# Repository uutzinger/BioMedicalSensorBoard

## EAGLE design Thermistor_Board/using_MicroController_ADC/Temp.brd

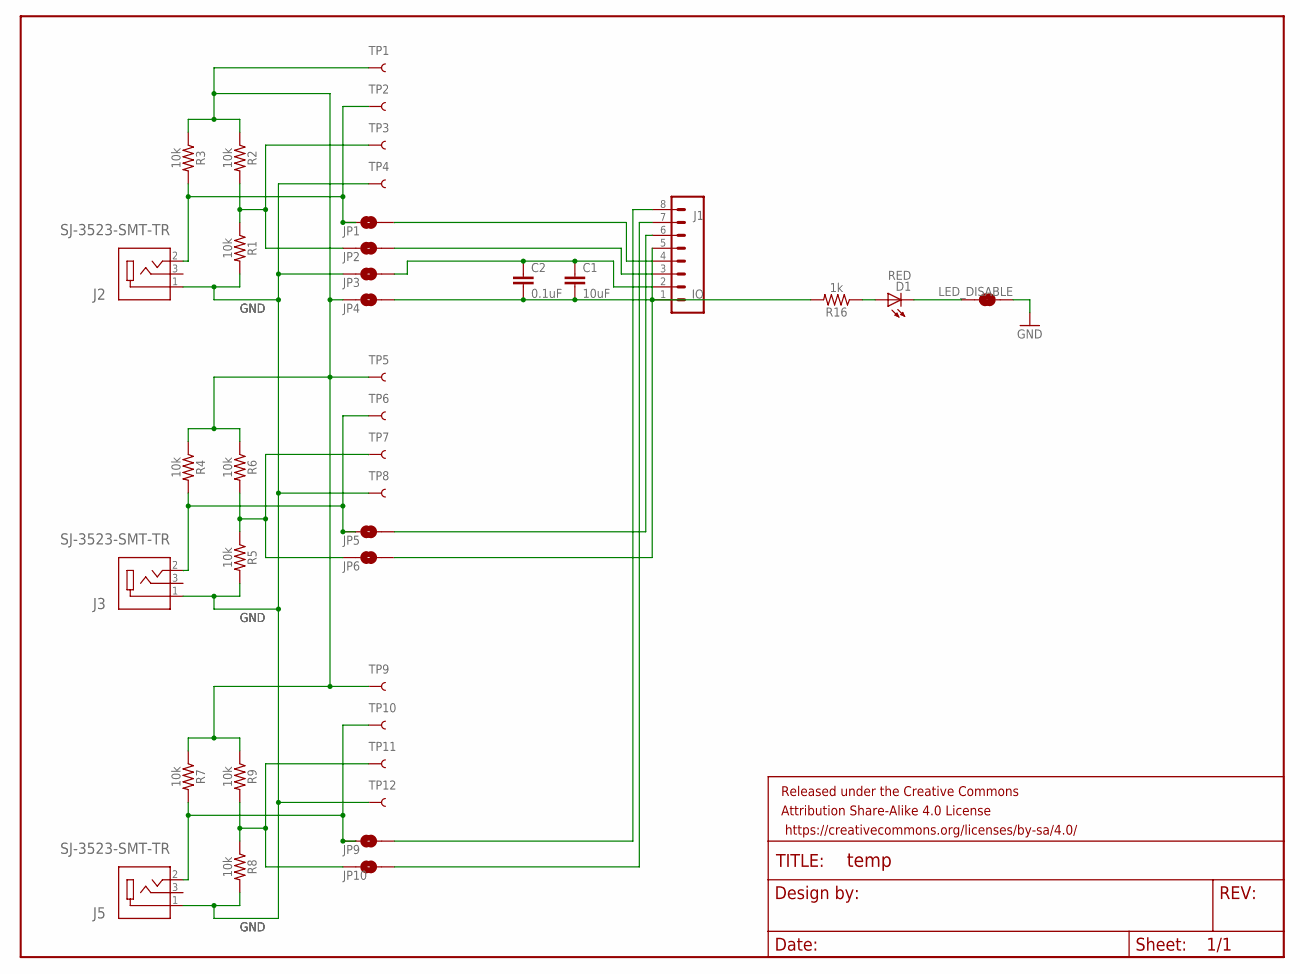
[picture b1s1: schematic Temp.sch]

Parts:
C1: 10uF; 0603
C2: 0.1uF; 0603
D1: RED; LED-0603
FRAME1: FRAME-LETTERNO_PACKAGE; DUMMY
J1: IO; 1X08
J2, J3, J5: SJ-3523-SMT-TR; CUI_SJ-3523-SMT-TR
JP1, JP2, JP3, JP4, JP5, JP6, JP9, JP10: JUMPER-SMT_2_NO_NO-SILK; SMT-JUMPER_2_NO_NO-SILK
LED_DISABLE: JUMPER-SMT_2_NC_TRACE_SILK; SMT-JUMPER_2_NC_TRACE_SILK
R1, R2, R3, R4, R5, R6, R7, R8, R9: 10k; 0603
R16: 1k; 0603
TP1, TP2, TP3, TP4, TP5, TP6, TP7, TP8, TP9, TP10, TP11, TP12: TEST-POINT3X5; PAD.03X.05

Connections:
3.3V: JP4.1, R2.1, R3.1, R4.1, R6.1, R7.1, R9.1, TP1.P$1, TP5.P$1, TP9.P$1
GND: J2.1, J3.1, J5.1, JP3.1, LED_DISABLE.1, R1.2, R5.2, R8.2, TP4.P$1, TP8.P$1, TP12.P$1
unnamed: JP6.1, R5.1, R6.2, TP7.P$1
unnamed: JP2.1, R1.1, R2.2, TP3.P$1
unnamed: J1.3, JP2.2
unnamed: J2.2, JP1.1, R3.2, TP2.P$1
unnamed: J1.4, JP1.2
unnamed: J3.2, JP5.1, R4.2, TP6.P$1
unnamed: J1.7, JP10.2
unnamed: J1.8, JP9.2
unnamed: J1.6, JP5.2
unnamed: JP10.1, R8.1, R9.2, TP11.P$1
unnamed: J5.2, JP9.1, R7.2, TP10.P$1
unnamed: C1.2, C2.2, J1.1, JP4.2, R16.2
unnamed: C1.1, C2.1, J1.2, J1.5, JP3.2, JP6.2
unnamed: D1.A, R16.1
unnamed: D1.C, LED_DISABLE.2

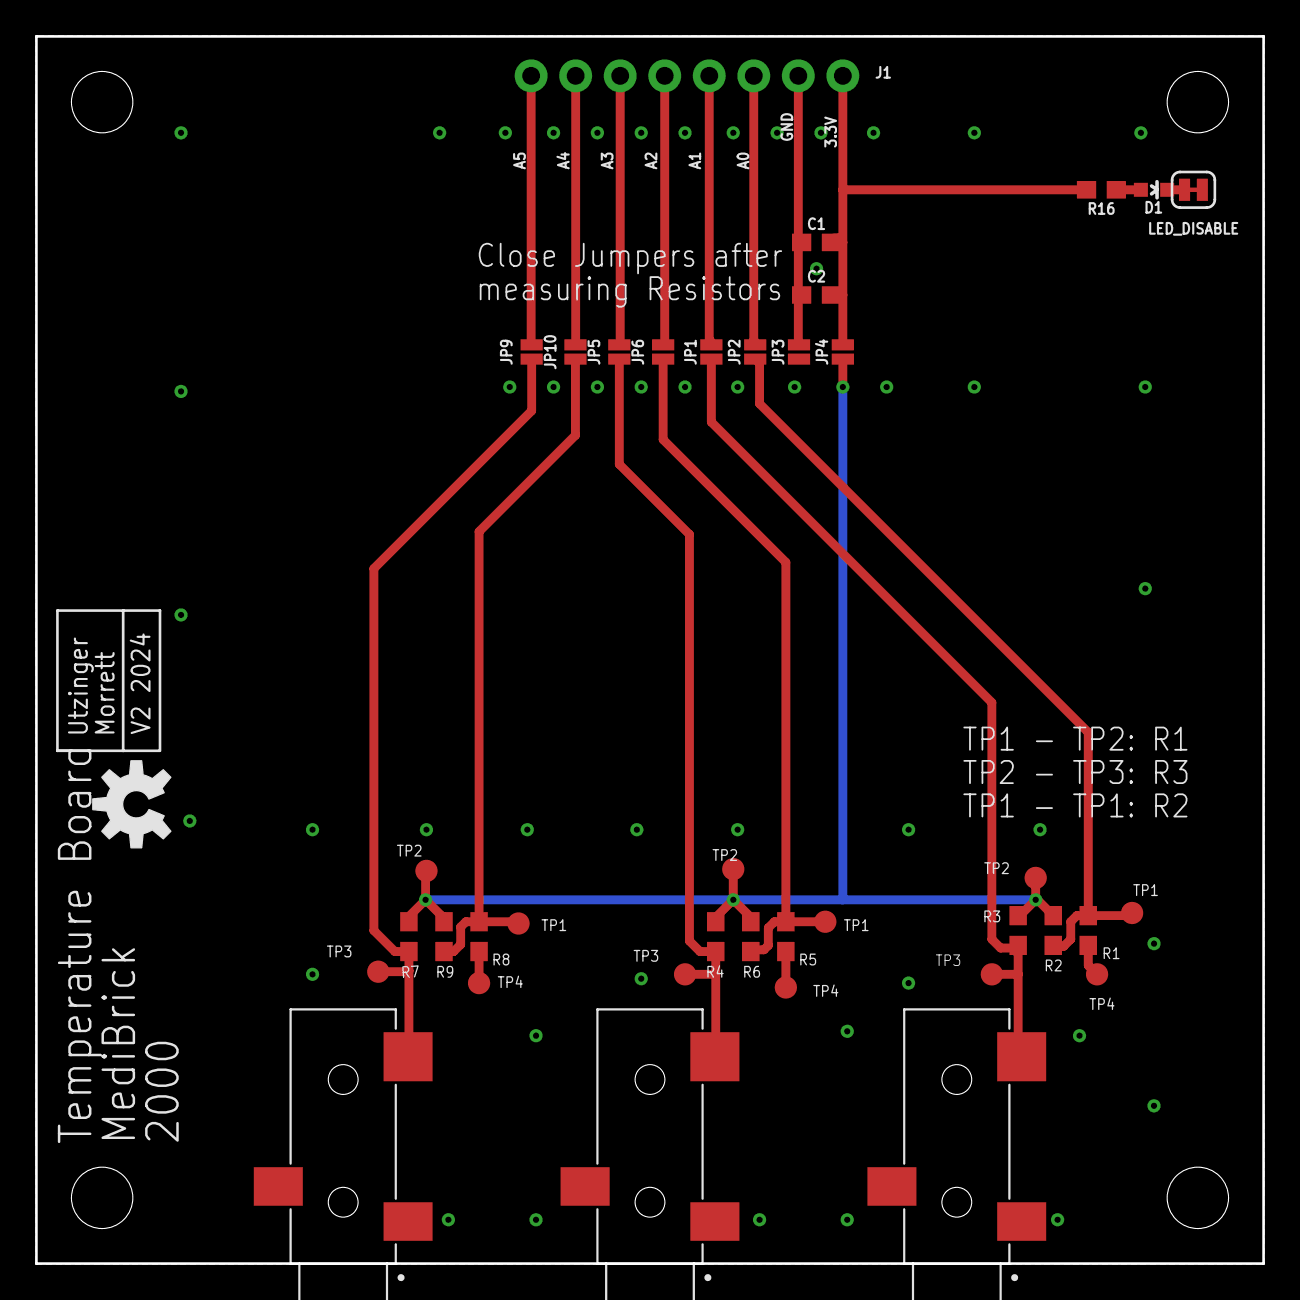
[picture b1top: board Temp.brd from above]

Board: 2 copper layers, 70.0 x 70.0 mm, 40 parts (1 on the bottom side), 17 nets.

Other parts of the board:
U$1: OSHW-LOGO-M

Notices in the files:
parts and their libraries:
SparkFun-Jumpers: Licensing: Creative Commons ShareAlike 4.0 International - https://creativecommons.org/licenses/by-sa/4.0
SparkFun-Aesthetics: Licensing: CC v3.0 Share-Alike You are welcome to use this library for commercial purposes.
SparkFun-Aesthetics: Released under the Creative Commons
